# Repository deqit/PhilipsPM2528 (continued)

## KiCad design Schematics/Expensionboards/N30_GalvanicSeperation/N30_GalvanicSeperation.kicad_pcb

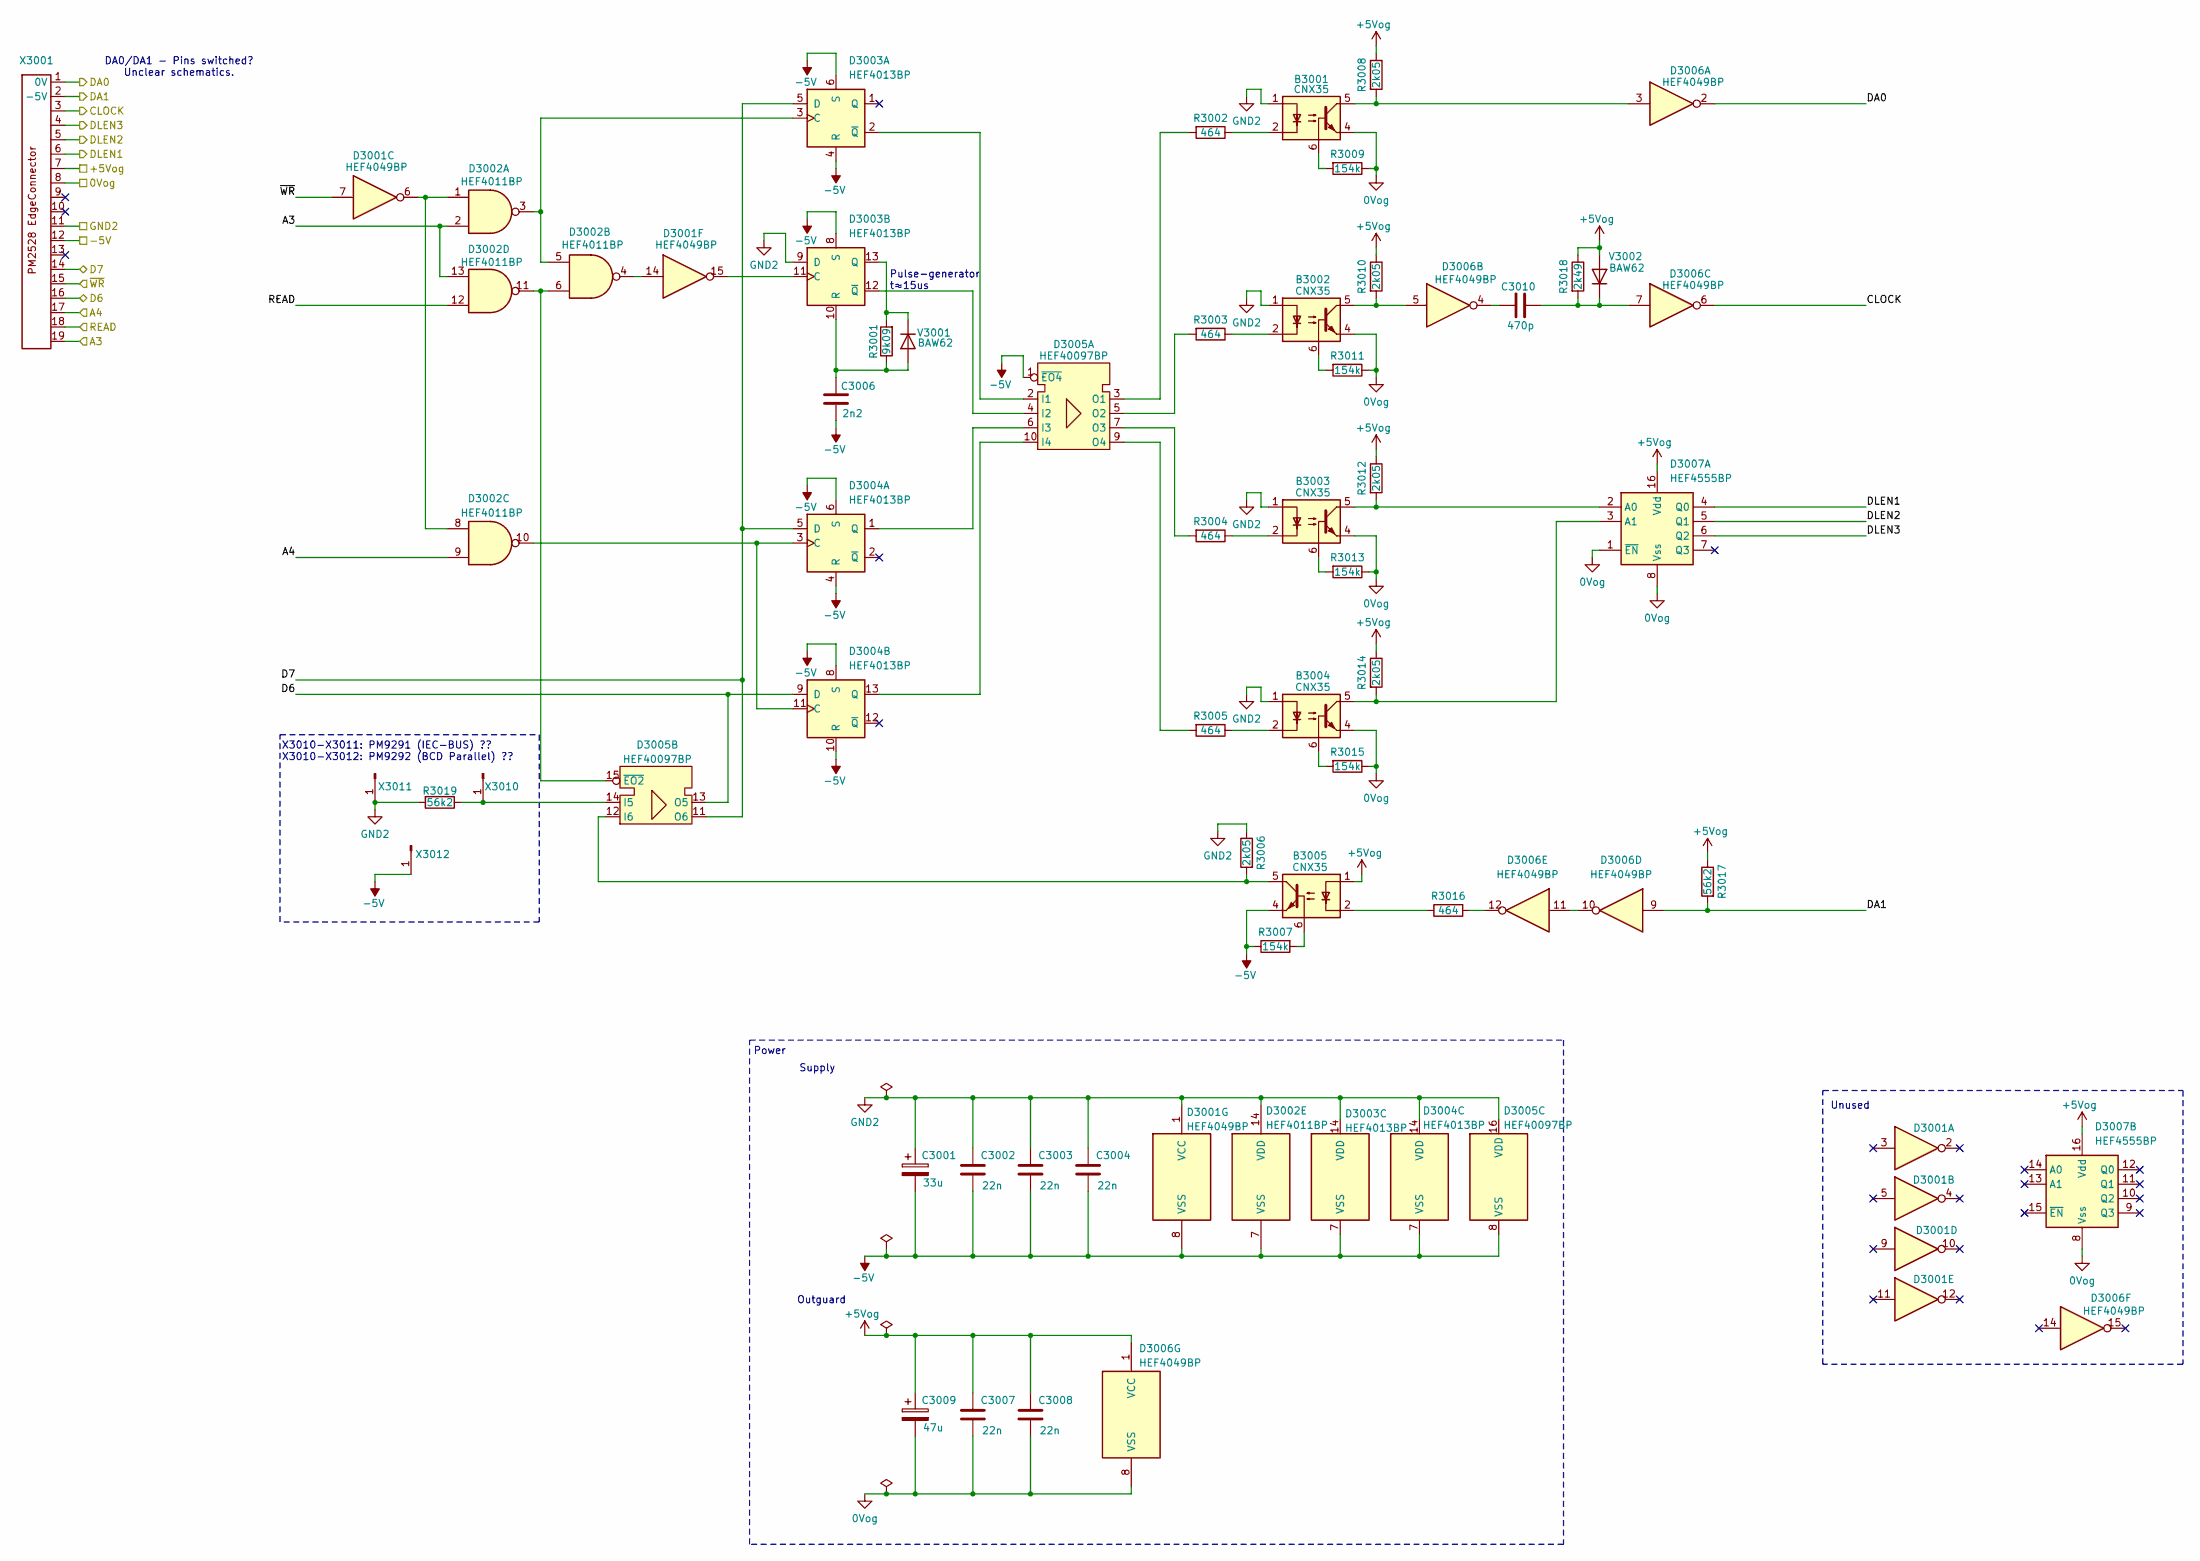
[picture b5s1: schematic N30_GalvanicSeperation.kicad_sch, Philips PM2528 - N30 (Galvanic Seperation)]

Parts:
B3001, B3002, B3003, B3004, B3005: CNX35; DIP-6_W7.62mm
C3001: 33u; CP_Radial_Tantal_D7.0mm_P5.00mm
C3002, C3003, C3004, C3007, C3008: 22n; C_Axial_L5.1mm_D3.1mm_P10.00mm_Horizontal
C3006: 2n2; C_Axial_L5.1mm_D3.1mm_P10.00mm_Horizontal
C3009: 47u; CP_Axial_L10.0mm_D6.0mm_P15.00mm_Horizontal
C3010: 470p; C_Axial_L5.1mm_D3.1mm_P10.00mm_Horizontal
D3001, D3006: HEF4049BP; DIP-16_W7.62mm
D3002: HEF4011BP; DIP-14_W7.62mm
D3003, D3004: HEF4013BP; DIP-14_W7.62mm
D3005: HEF40097BP; DIP-16_W7.62mm
D3007: HEF4555BP; DIP-16_W7.62mm
R3001: 9k09; R_Axial_DIN0207_L6.3mm_D2.5mm_P10.16mm_Horizontal
R3002, R3003, R3004, R3005, R3016: 464; R_Axial_DIN0207_L6.3mm_D2.5mm_P10.16mm_Horizontal
R3006, R3008, R3010, R3012, R3014: 2k05; R_Axial_DIN0207_L6.3mm_D2.5mm_P10.16mm_Horizontal
R3007, R3009, R3011, R3013, R3015: 154k; R_Axial_DIN0207_L6.3mm_D2.5mm_P10.16mm_Horizontal
R3017, R3019: 56k2; R_Axial_DIN0207_L6.3mm_D2.5mm_P10.16mm_Horizontal
R3018: 2k49; R_Axial_DIN0207_L6.3mm_D2.5mm_P10.16mm_Horizontal
V3001, V3002: BAW62; D_DO-35_SOD27_P7.62mm_Horizontal
X3001: PM2528_RiserCardConnector
X3010, X3011, X3012: Conn_01x01_MountingPin; Pin_D1.1mm_L8.5mm_W2.5mm_FlatFork

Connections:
0Vog: B3001.4, B3002.4, B3003.4, B3004.4, C3007.2, C3008.2, C3009.2, D3006.8 (VSS), D3007.1 (~EN), D3007.8 (Vss), R3009.1, R3011.1, R3013.1, R3015.1, X3001.8
+5Vog: B3005.1, C3007.1, C3008.1, C3009.1, D3006.1 (VCC), D3007.16 (Vdd), R3008.1, R3010.1, R3012.1, R3014.1, R3017.1, R3018.1, V3002.2 (A), X3001.7
-5V: B3005.4, C3001.2, C3002.2, C3003.2, C3004.2, C3006.2, D3001.8 (VSS), D3002.7 (VSS), D3003.4 (R), D3003.6 (S), D3003.7 (VSS), D3003.8 (S), D3004.4 (R), D3004.6 (S), D3004.7 (VSS), D3004.8 (S), D3004.10 (R), D3005.1 (~EO4), D3005.8 (VSS), R3007.1, X3001.12, X3012.1 (Pin_1_1)
/A3: D3002.2, D3002.13, X3001.19
/A4: D3002.9, X3001.17
/CLOCK: D3006.6, X3001.3
/D6: D3004.9 (D), D3005.13 (O5), X3001.16
/D7: D3003.5 (D), D3004.5 (D), D3005.11 (O6), X3001.14
/DA0: D3006.2, X3001.1 (0V)
/DA1: D3006.9, R3017.2, X3001.2 (-5V)
/DLEN1: D3007.4 (Q0), X3001.6
/DLEN2: D3007.5 (Q1), X3001.5
/DLEN3: D3007.6 (Q2), X3001.4
/READ: D3002.12, X3001.18
/~WR: D3001.7, X3001.15
GND2: B3001.1, B3002.1, B3003.1, B3004.1, C3001.1, C3002.1, C3003.1, C3004.1, D3001.1 (VCC), D3002.14 (VDD), D3003.9 (D), D3003.14 (VDD), D3004.14 (VDD), D3005.16 (VDD), R3006.1, R3019.2, X3001.11, X3011.1 (Pin_1_1)
unnamed: B3001.2, R3002.1
unnamed: B3001.5, D3006.3, R3008.2
unnamed: B3001.6, R3009.2
unnamed: B3002.2, R3003.1
unnamed: B3002.5, D3006.5, R3010.2
unnamed: B3002.6, R3011.2
unnamed: B3003.2, R3004.1
unnamed: B3003.6, R3013.2
unnamed: B3004.2, R3005.1
unnamed: B3004.6, R3015.2
unnamed: B3005.2, R3016.1
unnamed: B3005.6, R3007.2
unnamed: C3010.1, D3006.4
unnamed: D3001.6, D3002.1, D3002.8
unnamed: D3001.14, D3002.4
unnamed: D3002.3, D3002.5, D3003.3 (C)
unnamed: D3003.2 (~Q), D3005.2 (I1)
unnamed: D3001.15, D3003.11 (C)
unnamed: D3003.13 (Q), R3001.2, V3001.1 (K)
unnamed: C3006.1, D3003.10 (R), R3001.1, V3001.2 (A)
unnamed: D3003.12 (~Q), D3005.4 (I2)
unnamed: D3002.10, D3004.3 (C), D3004.11 (C)
unnamed: D3004.1 (Q), D3005.6 (I3)
unnamed: D3004.13 (Q), D3005.10 (I4)
unnamed: D3005.3 (O1), R3002.2
unnamed: D3005.5 (O2), R3003.2
unnamed: D3005.7 (O3), R3004.2
unnamed: D3005.9 (O4), R3005.2
unnamed: D3005.14 (I5), R3019.1, X3010.1 (Pin_1_1)
unnamed: B3005.5, D3005.12 (I6), R3006.2
unnamed: D3002.6, D3002.11, D3005.15 (~EO2)
unnamed: D3006.10, D3006.11
unnamed: D3006.12, R3016.2
unnamed: B3003.5, D3007.2 (A0), R3012.2
unnamed: B3004.5, D3007.3 (A1), R3014.2
unnamed: C3010.2, D3006.7, R3018.2, V3002.1 (K)

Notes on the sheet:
Unused
Outguard
Supply
Pulse-generator t≈15us
X3010-X3011: PM9291 (IEC-BUS) ?? X3010-X3012: PM9292 (BCD Parallel) ??
DA0/DA1 - Pins switched? Unclear schematics.
Power

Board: 2 copper layers, 46 parts (0 on the bottom side), 52 nets, no tracks yet.

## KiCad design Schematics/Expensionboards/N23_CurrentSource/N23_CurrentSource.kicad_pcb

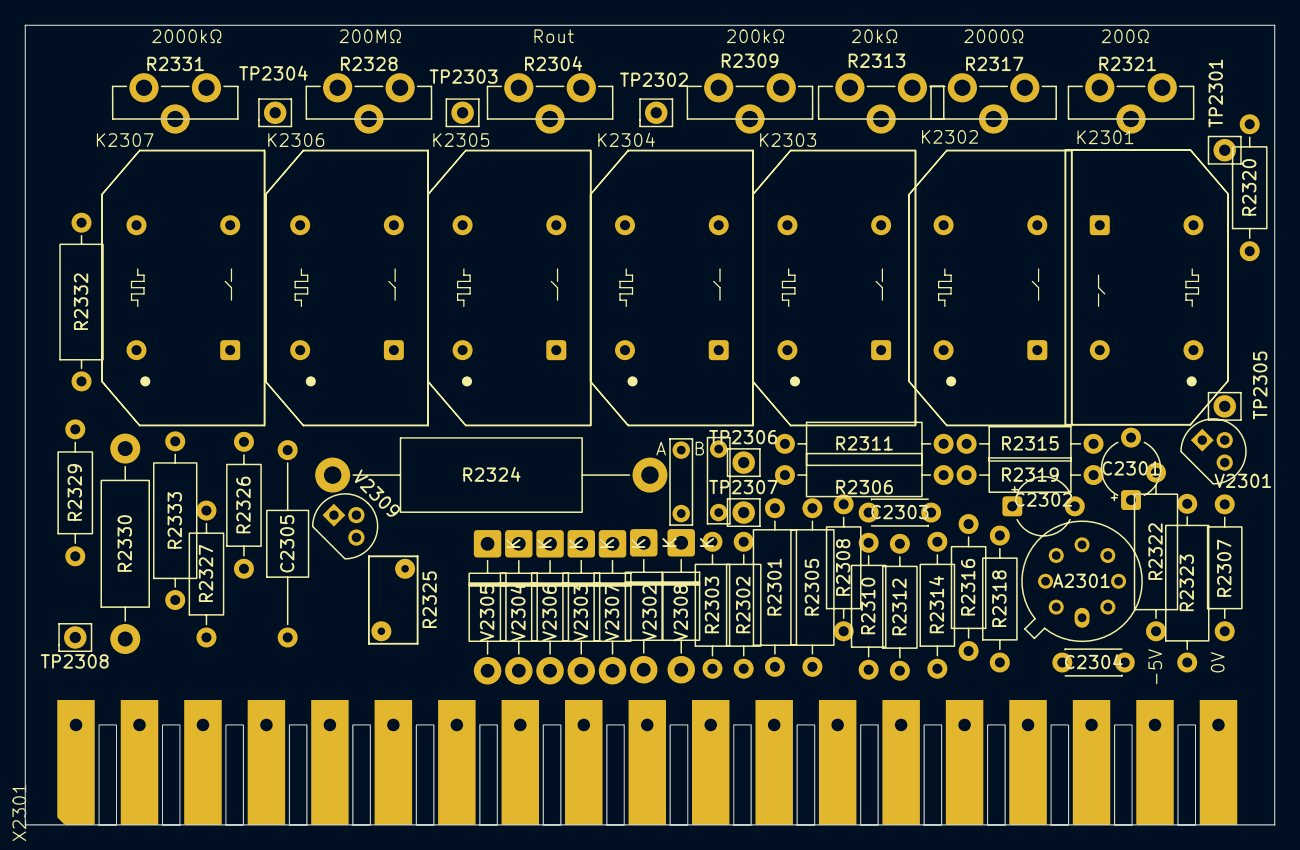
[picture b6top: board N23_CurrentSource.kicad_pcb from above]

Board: 2 copper layers, 100.0 x 64.0 mm, 66 parts (0 on the bottom side), 49 nets, no tracks yet.

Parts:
A2301: LM208AH; TO-99-8
C2301, C2302: 4u7; CP_Radial_Tantal_D4.5mm_P5.00mm
C2303: 100p; C_Disc_D4.3mm_W1.9mm_P5.00mm
C2304: 33p; C_Disc_D4.3mm_W1.9mm_P5.00mm
C2305: 1n33; C_Axial_L5.1mm_D3.1mm_P15.00mm_Horizontal
JP2301: B; TestPoint_Bridge_Pitch5.08mm_Drill0.7mm
JP2302: A; TestPoint_Bridge_Pitch5.08mm_Drill0.7mm
K2301, K2302, K2303, K2304, K2305, K2306, K2307: Reed relay assy
R2301: 487; R_Axial_DIN0309_L9.0mm_D3.2mm_P12.70mm_Horizontal
R2302: 487; R_Axial_DIN0207_L6.3mm_D2.5mm_P10.16mm_Horizontal
R2303: 200k; R_Axial_DIN0207_L6.3mm_D2.5mm_P10.16mm_Horizontal
R2304: 1K5; Trimmer vertical
R2305: 200k; R_Axial_DIN0309_L9.0mm_D3.2mm_P12.70mm_Horizontal
R2306: 402k; R_Axial_DIN0309_L9.0mm_D3.2mm_P12.70mm_Horizontal
R2307: 38k3; R_Axial_DIN0207_L6.3mm_D2.5mm_P10.16mm_Horizontal
R2308: 2k15; R_Axial_DIN0207_L6.3mm_D2.5mm_P10.16mm_Horizontal
R2309: 22k; Trimmer vertical
R2310: 2k8; R_Axial_DIN0207_L6.3mm_D2.5mm_P10.16mm_Horizontal
R2311: 357k; R_Axial_DIN0309_L9.0mm_D3.2mm_P12.70mm_Horizontal
R2312: 215; R_Axial_DIN0207_L6.3mm_D2.5mm_P10.16mm_Horizontal
R2313: 2k2; Trimmer vertical
R2314: 280; R_Axial_DIN0207_L6.3mm_D2.5mm_P10.16mm_Horizontal
R2315: 35k7; R_Axial_DIN0207_L6.3mm_D2.5mm_P10.16mm_Horizontal
R2316: 21R5; R_Axial_DIN0207_L6.3mm_D2.5mm_P10.16mm_Horizontal
R2317: 220; Trimmer vertical
R2318: 28; R_Axial_DIN0207_L6.3mm_D2.5mm_P10.16mm_Horizontal
R2319: 3k57; R_Axial_DIN0207_L6.3mm_D2.5mm_P10.16mm_Horizontal
R2320: 2R15; R_Axial_DIN0207_L6.3mm_D2.5mm_P10.16mm_Horizontal
R2321: 33; Trimmer vertical
R2322, R2323: 200; R_Axial_DIN0309_L9.0mm_D3.2mm_P12.70mm_Horizontal
R2324: 330; R_Axial_DIN0614_L14.3mm_D5.7mm_P25.40mm_Horizontal
R2325: 100; RV_Disc_D7mm_W3.9mm_P5mm
R2326: 898; R_Axial_DIN0207_L6.3mm_D2.5mm_P10.16mm_Horizontal
R2327: 3R32; R_Axial_DIN0207_L6.3mm_D2.5mm_P10.16mm_Horizontal
R2328: 100k; Trimmer vertical
R2329: 97k6; R_Axial_DIN0207_L6.3mm_D2.5mm_P10.16mm_Horizontal
R2330: 8M89; R_Axial_DIN0411_L9.9mm_D3.6mm_P15.24mm_Horizontal
R2331: 4k7; Trimmer vertical
R2332, R2333: 499k; R_Axial_DIN0309_L9.0mm_D3.2mm_P12.70mm_Horizontal
TP2301: 200Ω; Pin_D0.9mm_L10.0mm_W2.4mm_FlatFork
TP2302: MeasZero; Pin_D0.9mm_L10.0mm_W2.4mm_FlatFork
TP2303, TP2304, TP2305: Pin_D0.9mm_L10.0mm_W2.4mm_FlatFork
TP2306: +2VRefZero; Pin_D0.9mm_L10.0mm_W2.4mm_FlatFork
TP2307: +2VRef; Pin_D0.9mm_L10.0mm_W2.4mm_FlatFork
TP2308: Iout; Pin_D0.9mm_L10.0mm_W2.4mm_FlatFork
V2301: BC557B; TO-92
V2302, V2303, V2304, V2305, V2306, V2307, V2308: BAX12A; D_DO-41_SOD81_P10.16mm_Horizontal
V2309: BC337; TO-92
X2301: PM2528_RiserCardConnector

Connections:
+15V: A2301.7 (V+), C2302.1, R2307.1, X2301.4
-15V: A2301.4 (V-), C2301.2, X2301.3
/+2VRef: R2303.1, TP2307.1 (1_1), X2301.8
/+2VRefZero: R2304.1, R2304.2, TP2306.1 (1_1), X2301.9
/Filter: C2305.2, X2301.17
/Iout: R2325.2, R2330.2, R2333.2, TP2308.1 (1_1), X2301.19
/REL2301: K2301.10, V2302.2 (A), X2301.10
/REL2302: K2302.10, V2303.2 (A), X2301.11
/REL2303: K2303.10, V2304.2 (A), X2301.12
/REL2304: K2304.10, V2305.2 (A), X2301.13
/REL2305: K2305.10, V2306.2 (A), X2301.14
/REL2306: K2306.10, V2307.2 (A), X2301.15
/REL2307: K2307.10, V2308.2 (A), X2301.16
GND1: R2327.1, TP2302.1 (1_1), X2301.18
GND3: C2301.1, C2302.2, X2301.1 (0V_1)
GND4: K2301.6, K2302.6, K2303.6, K2304.6, K2305.6, K2306.6, K2307.6, V2302.1 (K), V2303.1 (K), V2304.1 (K), V2305.1 (K), V2306.1 (K), V2307.1 (K), V2308.1 (K), X2301.7
unnamed: A2301.3 (+), R2305.2, R2308.1, R2309.3
unnamed: A2301.2 (-), C2303.2, R2301.2, R2306.1
unnamed: A2301.1 (LOGIC_REFERENCE), C2304.1
unnamed: A2301.8 (~DISABLE), C2304.2
unnamed: C2303.1, R2306.2, R2307.2, R2323.1, TP2305.1 (1_1)
unnamed: C2305.1, K2305.1, R2324.1
unnamed: JP2301.1 (A_1), R2302.1, R2303.2
unnamed: JP2302.1 (A_1), R2301.1, R2302.2
unnamed: K2301.1, R2321.2, TP2301.1 (1_1)
unnamed: K2301.5, K2302.5, K2303.5, K2304.5, K2305.5, K2306.1, TP2303.1 (1_1)
unnamed: K2302.1, R2317.2
unnamed: K2303.1, R2313.2
unnamed: K2304.1, R2309.2
unnamed: K2306.5, K2307.1, R2326.2, R2328.1, TP2304.1 (1_1)
unnamed: K2307.5, R2331.1
unnamed: R2304.3, R2305.1
unnamed: R2308.2, R2309.1, R2310.1
unnamed: R2310.2, R2311.1
unnamed: R2311.2, R2312.1, R2313.3
unnamed: R2312.2, R2313.1, R2314.1
unnamed: R2314.2, R2315.1
unnamed: R2315.2, R2316.1, R2317.3
unnamed: R2316.2, R2317.1, R2318.1
unnamed: R2318.2, R2319.1
unnamed: R2319.2, R2320.1, R2321.3
unnamed: R2320.2, R2321.1, R2322.2
unnamed: R2322.1, R2323.2
unnamed: R2324.2, R2325.1
unnamed: R2326.1, R2327.2
unnamed: R2328.2, R2328.3, R2329.1
unnamed: R2329.2, R2330.1
unnamed: R2331.2, R2331.3, R2332.1
unnamed: R2332.2, R2333.1

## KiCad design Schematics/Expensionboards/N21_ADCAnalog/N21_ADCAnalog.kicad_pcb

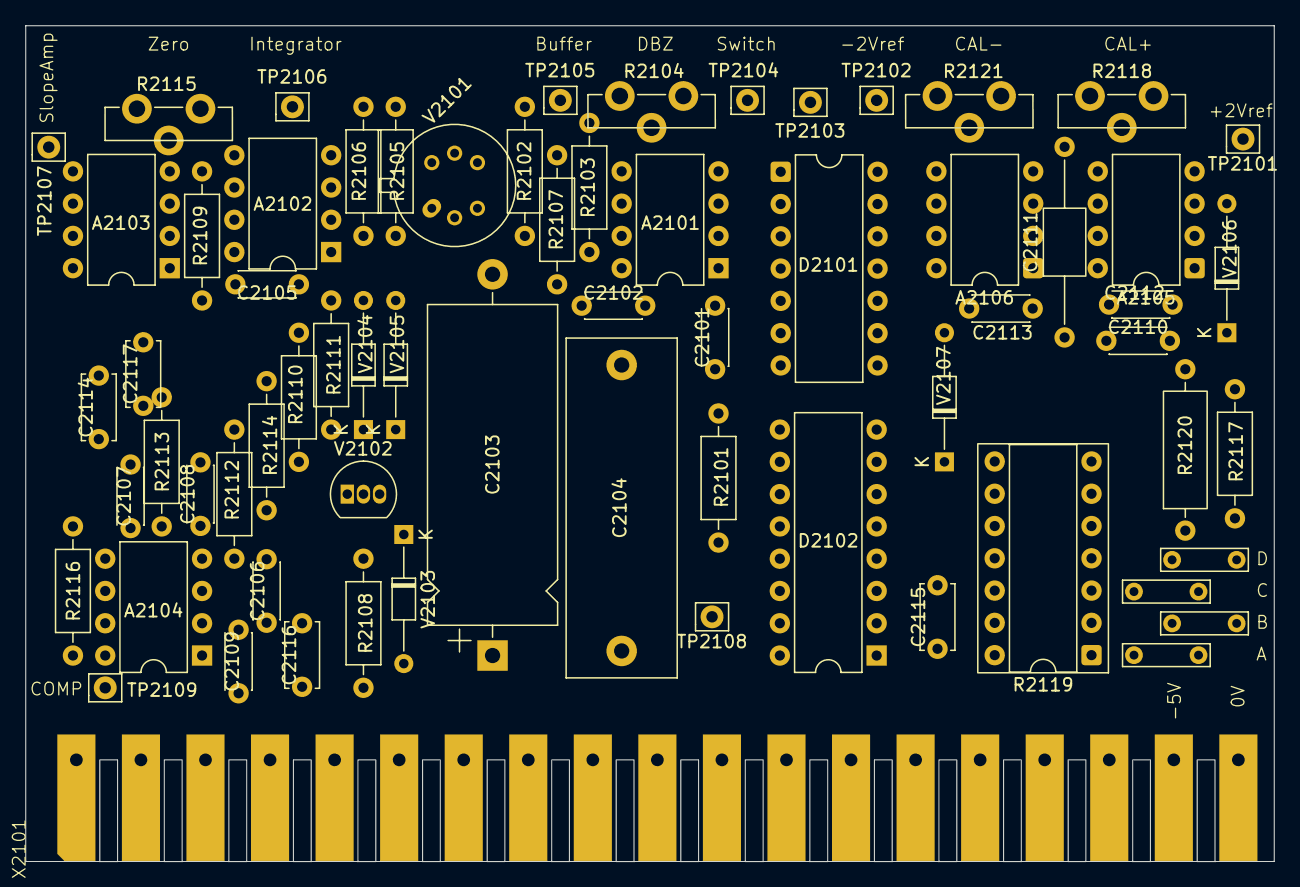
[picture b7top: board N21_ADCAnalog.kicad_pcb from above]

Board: 2 copper layers, 98.2 x 65.8 mm, 67 parts (0 on the bottom side), 54 nets, no tracks yet.

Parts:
A2101: LF356H; DIP-8_W7.62mm
A2102, A2106: LM201AN; DIP-8_W7.62mm
A2103: LF355H; DIP-8_W7.62mm
A2104: LM311N; DIP-8_W7.62mm
A2105: LM208AH; DIP-8_W7.62mm
C2101, C2102: 10n; C_Disc_D4.3mm_W1.9mm_P5.00mm
C2103: 162n; CP_Axial_L25.0mm_D10.0mm_P30.00mm_Horizontal
C2104: 3u3; C_Rect_L26.5mm_W8.5mm_P22.50mm_MKS4
C2105: 33p/100V; C_Disc_D4.3mm_W1.9mm_P5.00mm
C2106: 220p/500V; C_Disc_D4.3mm_W1.9mm_P5.00mm
C2107, C2108, C2109: 22n; C_Disc_D4.3mm_W1.9mm_P5.00mm
C2110: 4n7; C_Disc_D4.3mm_W1.9mm_P5.00mm
C2111: 4n22; C_Axial_L5.1mm_D3.1mm_P15.00mm_Horizontal
C2112, C2113: 33p; C_Disc_D4.3mm_W1.9mm_P5.00mm
C2114, C2117: 6u8; C_Disc_D5.0mm_W2.5mm_P5.00mm
C2115: 22u/10V; C_Disc_D5.0mm_W2.5mm_P5.00mm
C2116: 22u; C_Disc_D5.0mm_W2.5mm_P5.00mm
D2101: HEF4066; DIP-14_W7.62mm
D2102: HEF4104; DIP-16_W7.62mm
JP2101: A; TestPoint_Bridge_Pitch5.08mm_Drill0.7mm
JP2102: B; TestPoint_Bridge_Pitch5.08mm_Drill0.7mm
JP2103: C; TestPoint_Bridge_Pitch5.08mm_Drill0.7mm
JP2104: D; TestPoint_Bridge_Pitch5.08mm_Drill0.7mm
R2101: 8k66; R_Axial_DIN0207_L6.3mm_D2.5mm_P10.16mm_Horizontal
R2102: 140k; R_Axial_DIN0207_L6.3mm_D2.5mm_P10.16mm_Horizontal
R2103: 64k9; R_Axial_DIN0207_L6.3mm_D2.5mm_P10.16mm_Horizontal
R2104: 680k; Trimmer vertical
R2105, R2106: 21M1; R_Axial_DIN0207_L6.3mm_D2.5mm_P10.16mm_Horizontal
R2107: 24k9; R_Axial_DIN0207_L6.3mm_D2.5mm_P10.16mm_Horizontal
R2108: 40k2; R_Axial_DIN0207_L6.3mm_D2.5mm_P10.16mm_Horizontal
R2109: 5k9; R_Axial_DIN0207_L6.3mm_D2.5mm_P10.16mm_Horizontal
R2110: 121k; R_Axial_DIN0207_L6.3mm_D2.5mm_P10.16mm_Horizontal
R2111: 5k90; R_Axial_DIN0207_L6.3mm_D2.5mm_P10.16mm_Horizontal
R2112, R2113: 442; R_Axial_DIN0207_L6.3mm_D2.5mm_P10.16mm_Horizontal
R2114: 442k; R_Axial_DIN0207_L6.3mm_D2.5mm_P10.16mm_Horizontal
R2115: 47k; Trimmer vertical
R2116: 1k05; R_Axial_DIN0207_L6.3mm_D2.5mm_P10.16mm_Horizontal
R2117: 8k25; R_Axial_DIN0207_L6.3mm_D2.5mm_P10.16mm_Horizontal
R2118: 33; Trimmer vertical
R2119: OM528; DIP-14_W7.62mm_Socket
R2120: 590; R_Axial_DIN0309_L9.0mm_D3.2mm_P12.70mm_Horizontal
R2121: 100; Trimmer vertical
TP2101: +2Vref; Pin_D0.9mm_L10.0mm_W2.4mm_FlatFork
TP2102: -2Vref; Pin_D0.9mm_L10.0mm_W2.4mm_FlatFork
TP2103: 0Vref; Pin_D0.9mm_L10.0mm_W2.4mm_FlatFork
TP2104: Switch; Pin_D0.9mm_L10.0mm_W2.4mm_FlatFork
TP2105: Buffer; Pin_D0.9mm_L10.0mm_W2.4mm_FlatFork
TP2106: Integrator; Pin_D0.9mm_L10.0mm_W2.4mm_FlatFork
TP2107: Slope Amp; Pin_D0.9mm_L10.0mm_W2.4mm_FlatFork
TP2108: Input; Pin_D0.9mm_L10.0mm_W2.4mm_FlatFork
TP2109: Comp; Pin_D0.9mm_L10.0mm_W2.4mm_FlatFork
V2101: ON528; TO-78-6
V2102: BSV80; TO-92_Inline
V2103, V2104, V2105, V2106: BAW62; D_DO-34_SOD68_P10.16mm_Horizontal
V2107: BZV14; D_DO-34_SOD68_P10.16mm_Horizontal
X2101: PM2528_RiserCardConnector

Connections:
+5V: C2115.1, D2101.14 (VDD), D2102.1 (Vddo), X2101.5
+15V: A2101.7 (V+), A2102.7 (V+), A2103.7 (V+), A2104.8 (V+), A2105.7 (V+), A2106.7 (V+), C2101.2, C2107.1, C2114.1, R2107.1, R2115.1, R2117.2, X2101.4
-5V: A2104.1 (GND), C2109.2, C2116.2, D2101.7 (VSS), D2102.8 (Vss), X2101.2 (-5V)
-15V: A2101.4 (V-), A2102.4 (V-), A2103.4 (V-), A2104.4 (V-), A2105.4 (V-), A2106.4 (V-), C2102.2, C2108.2, C2117.2, R2105.2, R2106.2, R2115.3, X2101.3
/+2VRef: C2110.2, D2101.11, R2117.1, R2118.2, R2118.3, R2119.8, TP2101.1 (1_1), V2106.1 (K), X2101.7
/AZ: D2102.5, X2101.12
/COMP: A2104.7, R2116.2, TP2109.1 (1_1), X2101.19
/DN+: D2102.12, X2101.13
/DN-: D2102.4, X2101.11
/INPUT: R2101.1, TP2108.1 (1_1), X2101.9
/UP: D2102.11, X2101.14
/xAZ: D2101.5, D2102.6, V2103.1 (K)
/xDN+: D2101.12, D2102.13
/xDN-: D2101.6, D2102.3
/xUP: D2101.13, D2102.10
GND3: A2103.3 (+), C2104.2, C2110.1, C2111.2, D2101.4, D2102.15 (EN), D2102.16 (Vddi), R2113.2, R2119.10, TP2103.1 (1_1), X2101.6, X2101.8, X2101.10
GND4: C2101.1, C2102.1, C2107.2, C2108.1, C2109.1, C2114.2, C2115.2, C2116.1, C2117.1, R2108.2, R2116.1, V2104.1 (K), V2105.2 (A), X2101.1 (0V), X2101.18
unnamed: A2101.3 (+), D2101.2, D2101.3, D2101.9, D2101.10, TP2104.1 (1_1)
unnamed: A2101.2 (-), A2101.6, R2102.2, R2103.2, TP2105.1 (1_1)
unnamed: A2102.3 (+), R2106.1, V2101.4 (S)
unnamed: A2102.2 (-), R2105.1, V2101.1 (S)
unnamed: A2102.1 (BAL), C2105.1
unnamed: A2102.8 (C/B), C2105.2
unnamed: A2102.6, C2103.1, R2109.1, TP2106.1 (1_1)
unnamed: A2103.2 (-), R2109.2, R2110.1
unnamed: A2103.6, R2110.2, R2111.2, R2112.1, TP2107.1 (1_1)
unnamed: A2104.2 (+), C2106.2, R2104.1, R2104.2, R2113.1, R2114.1
unnamed: A2104.3 (-), C2106.1, R2112.2
unnamed: A2104.5 (BAL), A2104.6 (STRB)
unnamed: A2105.3 (+), R2119.6
unnamed: A2105.2 (-), A2106.2 (-), R2119.4
unnamed: A2105.1 (BAL), C2112.1
unnamed: A2105.8 (C/B), C2112.2
unnamed: A2106.3 (+), R2119.9
unnamed: A2106.1 (BAL), C2113.2
unnamed: A2106.8 (C/B), C2113.1
unnamed: C2103.2, R2102.1, V2101.3 (G)
unnamed: C2111.1, D2101.8, R2119.12, TP2102.1 (1_1)
unnamed: D2101.1, R2101.2
unnamed: JP2101.1 (A_1), JP2102.1 (A_1), R2119.14
unnamed: R2119.1, R2120.1
unnamed: JP2103.1 (A_1), R2119.2
unnamed: JP2104.1 (A_1), R2119.11
unnamed: R2118.1, R2119.5
unnamed: R2103.1, R2104.3
unnamed: R2107.2, V2101.2 (D), V2101.5 (D)
unnamed: R2114.2, R2115.2
unnamed: R2120.2, R2121.3
unnamed: R2111.1, V2102.1 (D), V2104.2 (A), V2105.1 (K)
unnamed: R2108.1, V2102.2 (G), V2103.2 (A)
unnamed: C2104.1, V2101.6 (G), V2102.3 (S)
unnamed: A2105.6, V2106.2 (A)
unnamed: A2106.6, R2121.1, R2121.2, V2107.2 (A)
unnamed: R2119.7, V2107.1 (K)

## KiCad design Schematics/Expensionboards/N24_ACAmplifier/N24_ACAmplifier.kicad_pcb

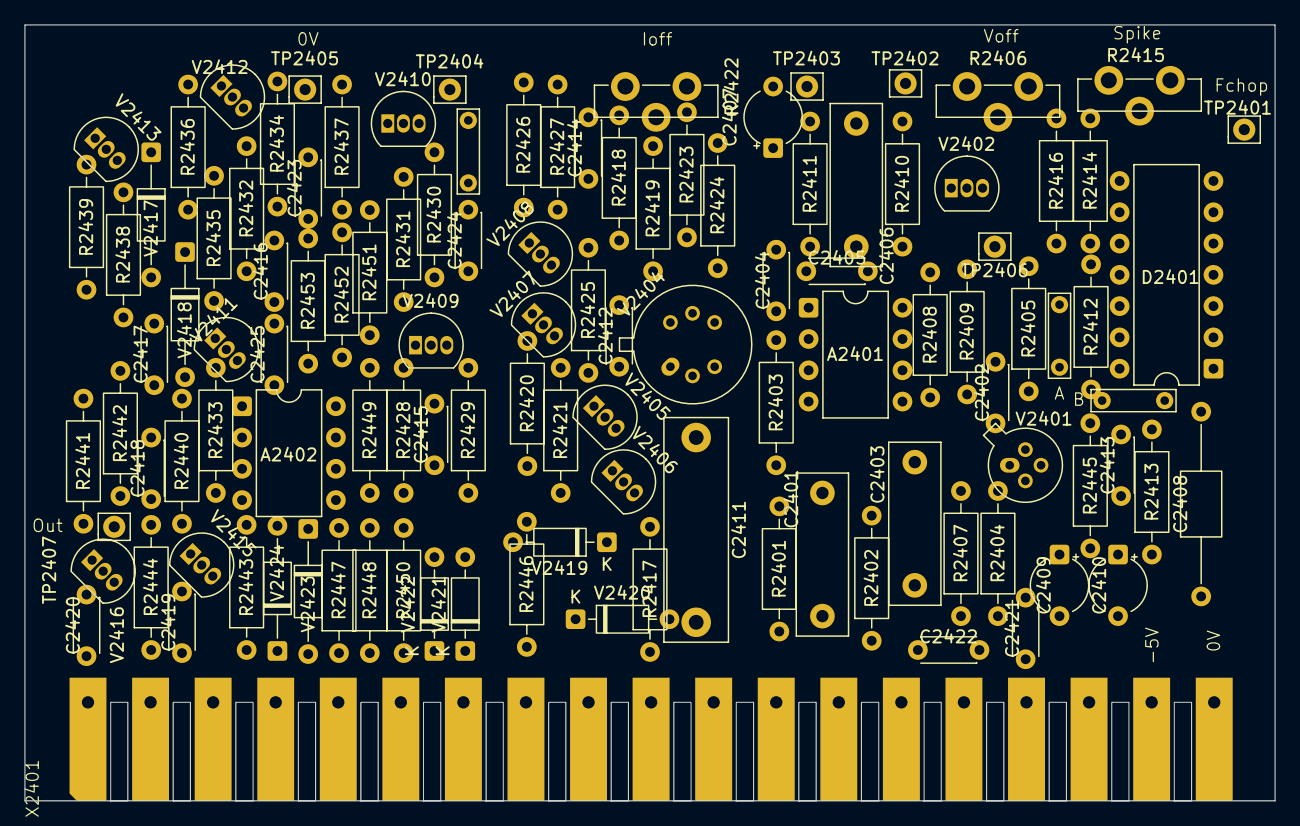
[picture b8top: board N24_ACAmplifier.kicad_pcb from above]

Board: 2 copper layers, 101.5 x 63.0 mm, 114 parts (0 on the bottom side), 60 nets, no tracks yet.

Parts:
A2401: LM308AH; DIP-8_W7.62mm
A2402: LM393N; DIP-8_W7.62mm
C2401: 22n; C_Rect_L13.0mm_W4.0mm_P10.00mm_FKS3_FKP3_MKS4
C2402: 8p2; C_Disc_D4.3mm_W1.9mm_P5.00mm
C2403: 33n; C_Rect_L13.0mm_W4.0mm_P10.00mm_FKS3_FKP3_MKS4
C2404: 220p; C_Disc_D4.3mm_W1.9mm_P5.00mm
C2405: 3p9; C_Disc_D4.3mm_W1.9mm_P5.00mm
C2406: 220n; C_Rect_L13.0mm_W4.0mm_P10.00mm_FKS3_FKP3_MKS4
C2407: 22u; CP_Radial_Tantal_D4.5mm_P5.00mm
C2408: 13n3; C_Axial_L5.1mm_D3.1mm_P15.00mm_Horizontal
C2409, C2410: 6u8; CP_Radial_Tantal_D4.5mm_P5.00mm
C2411: 330n; C_Rect_L18.0mm_W5.0mm_P15.00mm_FKS3_FKP3
C2412: 150p; C_Disc_D4.3mm_W1.9mm_P5.00mm
C2413, C2417: 10n; C_Disc_D4.3mm_W1.9mm_P5.00mm
C2414: 1n8; C_Disc_D4.3mm_W1.9mm_P5.00mm
C2415: 15p; C_Disc_D4.3mm_W1.9mm_P5.00mm
C2416: 12p; C_Disc_D4.3mm_W1.9mm_P5.00mm
C2418: 560p; C_Disc_D4.3mm_W1.9mm_P5.00mm
C2419, C2420: 6n8; C_Disc_D4.3mm_W1.9mm_P5.00mm
C2421, C2422, C2423, C2424: 22n; C_Disc_D4.3mm_W1.9mm_P5.00mm
C2425: 39p; C_Disc_D4.3mm_W1.9mm_P5.00mm
D2401: HEF4047; DIP-14_W7.62mm
JP1: Jumper_2_Small_Bridged; TestPoint_Bridge_Pitch5.08mm_Drill0.7mm
JP2401: A; TestPoint_Bridge_Pitch5.08mm_Drill0.7mm
JP2402: B; TestPoint_Bridge_Pitch5.08mm_Drill0.7mm
R2401, R2407, R2411: 1M00; R_Axial_DIN0207_L6.3mm_D2.5mm_P10.16mm_Horizontal
R2402: 95k3; R_Axial_DIN0207_L6.3mm_D2.5mm_P10.16mm_Horizontal
R2403: 9k53; R_Axial_DIN0207_L6.3mm_D2.5mm_P10.16mm_Horizontal
R2404: 15R4; R_Axial_DIN0207_L6.3mm_D2.5mm_P10.16mm_Horizontal
R2405, R2408: 681k; R_Axial_DIN0207_L6.3mm_D2.5mm_P10.16mm_Horizontal
R2406: 220k; Trimmer vertical
R2409, R2425: 2k74; R_Axial_DIN0207_L6.3mm_D2.5mm_P10.16mm_Horizontal
R2410, R2448: 15k4; R_Axial_DIN0207_L6.3mm_D2.5mm_P10.16mm_Horizontal
R2412, R2445, R2451, R2452: 1k05; R_Axial_DIN0207_L6.3mm_D2.5mm_P10.16mm_Horizontal
R2413: 634k; R_Axial_DIN0207_L6.3mm_D2.5mm_P10.16mm_Horizontal
R2414: 17k8; R_Axial_DIN0207_L6.3mm_D2.5mm_P10.16mm_Horizontal
R2415: 1k; Trimmer vertical
R2416, R2446: 1k21; R_Axial_DIN0207_L6.3mm_D2.5mm_P10.16mm_Horizontal
R2417, R2428: 10M; R_Axial_DIN0207_L6.3mm_D2.5mm_P10.16mm_Horizontal
R2418, R2419, R2423, R2449: 46k4; R_Axial_DIN0207_L6.3mm_D2.5mm_P10.16mm_Horizontal
R2420, R2421: 8k25; R_Axial_DIN0207_L6.3mm_D2.5mm_P10.16mm_Horizontal
R2422: 150; Trimmer vertical
R2424: 10k; R_Axial_DIN0207_L6.3mm_D2.5mm_P10.16mm_Horizontal
R2426: 1k78; R_Axial_DIN0207_L6.3mm_D2.5mm_P10.16mm_Horizontal
R2427: 140; R_Axial_DIN0207_L6.3mm_D2.5mm_P10.16mm_Horizontal
R2429: 301k; R_Axial_DIN0207_L6.3mm_D2.5mm_P10.16mm_Horizontal
R2430: 60k4; R_Axial_DIN0207_L6.3mm_D2.5mm_P10.16mm_Horizontal
R2431, R2437: 2k15; R_Axial_DIN0207_L6.3mm_D2.5mm_P10.16mm_Horizontal
R2432: 205; R_Axial_DIN0207_L6.3mm_D2.5mm_P10.16mm_Horizontal
R2433: 2k61; R_Axial_DIN0207_L6.3mm_D2.5mm_P10.16mm_Horizontal
R2434: 2k37; R_Axial_DIN0207_L6.3mm_D2.5mm_P10.16mm_Horizontal
R2435, R2436: 7R5; R_Axial_DIN0207_L6.3mm_D2.5mm_P10.16mm_Horizontal
R2438: 4k64; R_Axial_DIN0207_L6.3mm_D2.5mm_P10.16mm_Horizontal
R2439: 215; R_Axial_DIN0207_L6.3mm_D2.5mm_P10.16mm_Horizontal
R2440, R2441, R2443, R2444: 71R5; R_Axial_DIN0207_L6.3mm_D2.5mm_P10.16mm_Horizontal
R2442: 21R15; R_Axial_DIN0207_L6.3mm_D2.5mm_P10.16mm_Horizontal
R2447: 15K4; R_Axial_DIN0207_L6.3mm_D2.5mm_P10.16mm_Horizontal
R2450, R2453: 30k1; R_Axial_DIN0207_L6.3mm_D2.5mm_P10.16mm_Horizontal
TP2401: Fchop; Pin_D0.9mm_L10.0mm_W2.4mm_FlatFork
TP2402, TP2403: Pin_D0.9mm_L10.0mm_W2.4mm_FlatFork
TP2404: something; Pin_D0.9mm_L10.0mm_W2.4mm_FlatFork
TP2405: 0V; Pin_D0.9mm_L10.0mm_W2.4mm_FlatFork
TP2406: AC_RMS?; Pin_D0.9mm_L10.0mm_W2.4mm_FlatFork
TP2407: OUT; Pin_D0.9mm_L10.0mm_W2.4mm_FlatFork
V2401: BSV81; TO-72-4
V2402: BFW13; TO-92_Inline
V2404: BFQ14; TO-75-6
V2405, V2406, V2413: BC547B; TO-92_Inline
V2407, V2408: BC557B; TO-92_Inline
V2409, V2410: BFW11; TO-92_Inline
V2411, V2412, V2415: BF199; TO-92_Inline
V2416: BF324; TO-92_Inline
V2417: BZX79-C3V0; D_DO-35_SOD27_P10.16mm_Horizontal
V2418: BZX46-C2V0; D_DO-35_SOD27_P10.16mm_Horizontal
V2419, V2420: BAV45; D_DO-35_SOD27_P7.62mm_Horizontal
V2421, V2422: BAW62; D_DO-35_SOD27_P7.62mm_Horizontal
V2423, V2424: BZX79-B8V2; D_DO-35_SOD27_P10.16mm_Horizontal
X2401: PM2528_RiserCardConnector

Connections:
+15V: A2401.7 (V+), A2402.8 (V+), C2409.1, C2419.2, C2421.1, C2423.1, R2406.1, R2418.2, R2419.2, R2425.2, R2433.2, R2434.2, R2447.2, R2453.1, X2401.4
-5V: C2413.1, D2401.7 (VSS), D2401.8 (+TRIGGER), D2401.9 (EXT_RESET), D2401.12 (RETRIGGER), X2401.2 (-5V)
-15V: A2401.4 (V-), A2402.4 (V-), C2410.2, C2420.1, C2422.2, C2424.2, C2425.1, R2406.3, R2423.1, R2426.1, R2430.1, R2431.1, R2437.1, R2439.1, R2448.1, R2450.1, V2417.2 (A), X2401.3
/CFI: A2402.1, A2402.7, C2425.2, R2449.2, X2401.14
/IN: C2411.2, R2401.1, V2419.2 (A), V2420.1 (K), X2401.10
/OUT: C2418.1, R2443.1, R2444.2, TP2407.1 (1_1), V2423.2 (A), V2424.1 (K), X2401.17
GND2: C2413.2, C2414.1, D2401.4 (~ASTABLE), D2401.5 (ASTABLE), D2401.6 (-TRIGGER), D2401.14 (VDD), R2417.1, R2420.1, R2421.1, R2429.1, R2449.1, R2451.1, R2452.1, V2409.2 (S), V2410.2 (S), X2401.1 (0V)
GND3: C2401.2, C2404.2, R2404.1, R2407.1, R2409.1, R2446.1, X2401.6
GND4: C2407.2, V2402.2 (S), X2401.9, X2401.11
GND5: R2438.1, R2445.2, TP2405.1 (1_1), X2401.13
GND6: C2409.2, C2410.1, C2419.1, C2420.2, C2421.2, C2422.1, C2423.2, C2424.1, X2401.19
unnamed: A2401.3 (+), C2404.1, R2403.2
unnamed: A2401.2 (-), R2408.1, R2409.2
unnamed: A2401.1 (CompenA), C2405.1
unnamed: A2401.8 (CompenB), C2405.2
unnamed: A2401.6, C2406.1, R2408.2, TP2406.1 (1_1)
unnamed: A2402.3 (+), R2452.2, R2453.2
unnamed: A2402.2 (-), R2448.2, V2422.2 (A), V2424.2 (A)
unnamed: A2402.5 (+), R2447.1, V2421.1 (K), V2423.1 (K)
unnamed: A2402.6 (-), R2450.2, R2451.2
unnamed: C2401.1, R2401.2, R2402.1
unnamed: C2402.1, R2415.2
unnamed: C2403.2, R2403.1, R2407.2
unnamed: C2406.2, R2410.1
unnamed: C2407.1, R2411.2, R2424.1, TP2403.1 (1_1)
unnamed: C2411.1, C2415.1, R2417.2, V2404.3 (G)
unnamed: C2414.2, R2427.1
unnamed: C2416.1, R2432.1
unnamed: C2418.2, R2442.2
unnamed: C2408.1, D2401.1 (C)
unnamed: D2401.10 (Q), R2414.1, TP2401.1 (1_1), V2402.1 (G)
unnamed: D2401.2 (R), R2413.2
unnamed: C2408.2, D2401.3 (RC_COMMON), R2413.1
unnamed: D2401.11 (~Q), V2401.2 (G)
unnamed: JP1.1 (A_1), R2426.2, R2427.2
unnamed: TP2404.1 (1_1), V2410.1 (G)
unnamed: JP2401.1 (A_1), R2412.1, R2416.2
unnamed: JP2402.1 (A_1), R2412.2, R2445.1
unnamed: R2405.2, R2406.2
unnamed: R2414.2, R2415.3
unnamed: R2415.1, R2416.1
unnamed: R2422.1, V2404.4 (S)
unnamed: R2422.2, R2423.2
unnamed: R2422.3, V2404.1 (S)
unnamed: R2424.2, V2404.6 (G)
unnamed: R2428.1, R2429.2, R2430.2
unnamed: R2404.2, R2405.1, V2401.3 (S), V2401.4 (Bulk)
unnamed: C2402.2, C2403.1, R2402.2, V2401.1 (D)
unnamed: R2410.2, R2411.1, TP2402.1 (1_1), V2402.3 (D)
unnamed: C2412.2, R2418.1, V2404.2 (D)
unnamed: C2412.1, R2419.1, V2404.5 (D)
unnamed: R2431.2, V2409.3 (D)
unnamed: C2415.2, R2428.2, V2409.1 (G)
unnamed: R2437.2, V2410.3 (D)
unnamed: C2416.2, C2417.1, R2441.1, R2442.1, V2418.1 (K)
unnamed: R2432.2, R2434.1
unnamed: R2438.2, V2417.1 (K)
unnamed: R2435.2, R2436.1
unnamed: C2417.2, R2433.1, R2440.1, V2418.2 (A)
unnamed: R2446.2, V2419.1 (K), V2420.2 (A), V2421.2 (A), V2422.1 (K)

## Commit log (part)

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2024-08-15 Added README.md
2024-08-15 First version
2024-08-15 Added gitignore
2024-08-15 Deleted PM2528Riser-backups
2024-08-29 Version 2
2024-08-29 Remove backups
2024-08-29 Removed backups
2024-08-29 Added new files for N21
2024-08-29 Remove cache-files
2024-08-29 Deleted fp-info-cache
2024-08-29 Expanded .gitignore
2024-10-04 Replaced testpins with testloops/beads
2024-11-01 Added N22/N23
2024-11-01 Reformat folders
2025-04-08 Updates, add N25
2025-04-27 Updated info, updated N22
2025-05-25 Started with N24
2025-05-29 Small updates, N25 also
2025-05-30 N25 RMS Ok!
2025-05-30 Updated relais-xreference
2025-07-06 Update schematics, move projectlibraries to D:
2025-07-24 Restructure folders, added EPROM-dumps
2025-07-28 Restructure folders, added EPROMs and Ghidra-project
2025-08-05 Lotsofchanges. Included Ghidra-project and correct firmware-images
2025-08-08 Reworked N20/N21
2025-08-08 Added readme.
2025-08-08 Added Ghidra-stuff
2025-08-08 Restructure folders
2025-08-08 Remove obsolete files
2025-08-10 Small modifications, more disassembly
2025-08-10 Reorganize Ghidra folderstructure Add some comments in assembly
2025-08-15 Updated N24 schema/PCB
2025-08-17 Updated some component-values
2025-08-17 Added N30 schema/PCB Small additions to disassembly
2025-08-23 Updated disassembly some more Moved PM2528 footprints/3D to subfolder
2025-08-31 More disassembly More info in Info-Excel-sheet
2025-09-10 Some more disassembly
2025-09-12 Some more disassembly, optimize N20 schematics (naming of signals)
2025-09-13 Lotsadisassembly
2025-09-21 Small updates Some GPIB-analyzing-functions found.
2025-10-05 Added a simple POC-ROM (counting from 9 to 1)
2025-10-10 Lotsofassembly-comments Added extra MCS48-info Updated Excelsheet
2025-10-17 Added LA-traces, some assembly-comments
2025-10-19 Add link to hackaday.io
2025-11-02 Added ADC controlflow (Archimate)
2025-11-02 Deepdive ADC (wip)
2025-11-15 Added ADC-deepdive txts
2025-11-15 Deepdive - added more text/images
2025-11-18 Created new screenshots, removed todo-part of the text. Still todo.
2025-11-18 Removed one paragraph
2025-11-19 Removed Temp-files
2025-11-19 Added N20 deepdive
2025-11-29 Small textual changes
2025-11-29 Added N21 deepdive
2025-11-29 General info added
2025-11-29 Fixed type
2025-11-29 Small things
2025-11-30 Included signal-names
2025-11-30 Filerename-typo
2025-11-30 Included schematics
2025-12-03 Added PCB
2025-12-03 Rename ADC Core to ADC Analog
2025-12-03 Textual changes
2025-12-03 Included PCBs, Risercard and 3D-views
2025-12-03 PCBs in color
2025-12-16 Schematic-analyses N20
2025-12-16 tempfiles
2025-12-21 More N20
2026-01-13 name of section
2026-01-16 More N20, update Ghidra-project to most recent Ghidra version
